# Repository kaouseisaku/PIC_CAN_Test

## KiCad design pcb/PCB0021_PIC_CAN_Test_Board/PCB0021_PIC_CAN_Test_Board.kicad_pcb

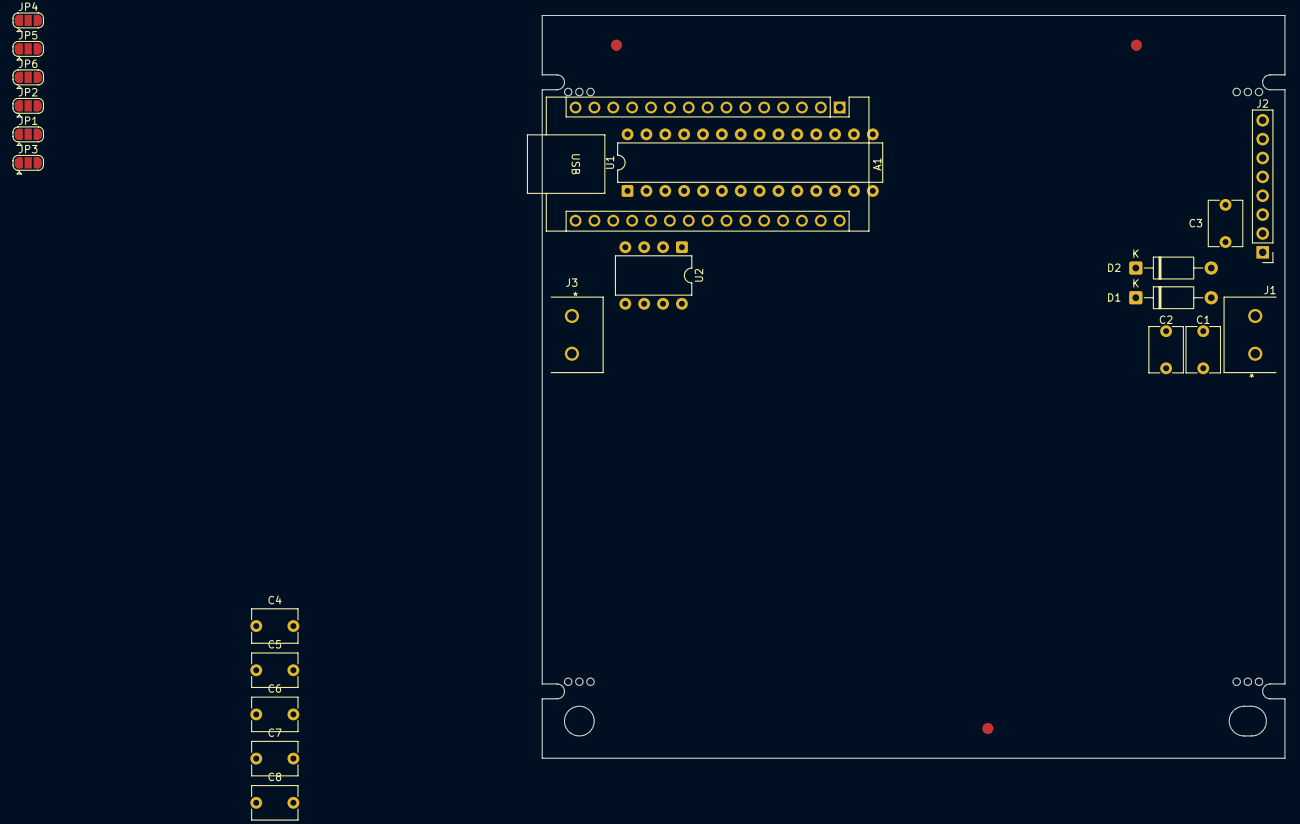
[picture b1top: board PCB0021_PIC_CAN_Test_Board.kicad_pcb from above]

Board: 2 copper layers, 100.0 x 100.0 mm, 22 parts (0 on the bottom side), 38 nets, no tracks yet.

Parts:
A1: Arduino_Nano_v3.x; Arduino_Nano
C1: 106C10; C_Disc_D6.0mm_W4.4mm_P5.00mm
C2, C3, C4, C5, C6, C7, C8: 104C10; C_Disc_D6.0mm_W4.4mm_P5.00mm
D1, D2: SBM245L; D_A-405_P10.16mm_Horizontal
J1, J3: TB111-2-2-E-1-1; TB111-2-2-X-1-1
J2: PH-1; PinHeader_1x08_P2.54mm_Vertical
JP1, JP2, JP3, JP4, JP5, JP6: Jumper_3_Open; SolderJumper-3_P1.3mm_Open_RoundedPad1.0x1.5mm
U1: PIC18F26K80_ISP; DIP-28_W7.62mm
U2: MCP2562-E-P; DIP-8_W7.62mm

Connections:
+5V: A1.27 (+5V), C4.1, C5.1, C6.1, C7.1, C8.1, D1.1 (K), D2.1 (K), U1.6 (Vcap), U1.20 (Vdd), U2.3 (VDD), U2.5 (Vio)
/AN0: A1.19 (A0), U1.2 (RA0/AN0)
/AN1: A1.20 (A1), U1.3 (RA1/AN1)
/AN2: A1.21 (A2), U1.4 (RA2/Vref-/AN2)
/AN3: A1.22 (A3), U1.5 (RA3/Vref+/AN3)
/CANRX: JP2.1 (A), U2.4 (RXD)
/CANRX/RB3: JP2.2 (C), U1.24 (CANRX/INT3/RB3)
/CANSTBY: JP3.1 (A), U2.8 (STBY)
/CANSTBY/RB4: JP3.2 (C), U1.25 (AN9/ECCP1/RB4)
/CANTX: JP1.1 (A), U2.1 (TXD)
/CANTX/RB2: JP1.2 (C), U1.23 (CANTX/INT2/RB2)
/PCG: J2.5, U1.27 (PGC/TX2/RB6)
/PGD: J2.4, U1.28 (PGD/RX2/RB7)
/RB0: A1.5 (D2), U1.21 (AN10/INT0/RB0)
/RB1: A1.6 (D3), U1.22 (AN8/INT1/RB1)
/RB2: A1.7 (D4), JP1.3 (B)
/RB3: A1.8 (D5), JP2.3 (B)
/RB4: A1.9 (D6), JP3.3 (B)
/RB5: A1.10 (D7), U1.26 (CCP5/RB5)
/RC0: A1.11 (D8), U1.11 (SOSCO/RC0)
/RC1: A1.12 (D9), U1.12 (SOSCI/RC1)
/RC2: A1.13 (D10), U1.13 (CCP2/RC2)
/SCK: A1.16 (D13), JP4.1 (A)
/SCL: A1.24 (A5), JP4.3 (B)
/SCL/SCK: JP4.2 (C), U1.14 (SCL/SCK/RC3)
/SDA: A1.23 (A4), JP5.3 (B)
/SDA/SDI: JP5.2 (C), U1.15 (SDA/SDI/RC4)
/SDI: A1.14 (D11), JP5.1 (A)
/SDO: A1.15 (D12), JP6.1 (A)
/SDO/RC5: JP6.2 (C), U1.16 (SDO/RC5)
/UART_RX: A1.2 (D0/RX), U1.18 (CANRX/RX1/CCP4/RC7)
/UART_TX: A1.1 (D1/TX), U1.17 (CANTX/TX1/CCP3/RC6)
/~MCLR: A1.3 (~RESET), A1.28 (~RESET), J2.1, U1.1 (~MCLR/RE3)
GND: A1.4 (GND), A1.29 (GND), C1.2, C2.2, C3.2, C4.2, C5.2, C6.2, C7.2, C8.2, J1.1, J2.3, U1.8 (Vss), U1.19 (Vss), U2.2 (VSS)
unnamed: J3.1, U2.7 (CANH)
unnamed: J3.2, U2.6 (CANL)
VIN1: C1.1, C2.1, D1.2 (A), J1.2
VIN2: C3.1, D2.2 (A), J2.2

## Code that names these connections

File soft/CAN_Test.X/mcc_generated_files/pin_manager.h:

/**
  @Generated Pin Manager Header File

  @Company:
    Microchip Technology Inc.

  @File Name:
    pin_manager.h

  @Summary:
    This is the Pin Manager file generated using PIC10 / PIC12 / PIC16 / PIC18 MCUs

  @Description
    This header file provides APIs for driver for .
    Generation Information :
        Product Revision  :  PIC10 / PIC12 / PIC16 / PIC18 MCUs - 1.81.8
        Device            :  PIC18F26K80
        Driver Version    :  2.11
    The generated drivers are tested against the following:
        Compiler          :  XC8 2.36 and above
        MPLAB 	          :  MPLAB X 6.00	
*/

/*
    (c) 2018 Microchip Technology Inc. and its subsidiaries. 
    
    Subject to your compliance with these terms, you may use Microchip software and any 
    derivatives exclusively with Microchip products. It is your responsibility to comply with third party 
    license terms applicable to your use of third party software (including open source software) that 
    may accompany Microchip software.
    
    THIS SOFTWARE IS SUPPLIED BY MICROCHIP "AS IS". NO WARRANTIES, WHETHER 
    EXPRESS, IMPLIED OR STATUTORY, APPLY TO THIS SOFTWARE, INCLUDING ANY 
    IMPLIED WARRANTIES OF NON-INFRINGEMENT, MERCHANTABILITY, AND FITNESS 
    FOR A PARTICULAR PURPOSE.
    
    IN NO EVENT WILL MICROCHIP BE LIABLE FOR ANY INDIRECT, SPECIAL, PUNITIVE, 
    INCIDENTAL OR CONSEQUENTIAL LOSS, DAMAGE, COST OR EXPENSE OF ANY KIND 
    WHATSOEVER RELATED TO THE SOFTWARE, HOWEVER CAUSED, EVEN IF MICROCHIP 
    HAS BEEN ADVISED OF THE POSSIBILITY OR THE DAMAGES ARE FORESEEABLE. TO 
    THE FULLEST EXTENT ALLOWED BY LAW, MICROCHIP'S TOTAL LIABILITY ON ALL 
    CLAIMS IN ANY WAY RELATED TO THIS SOFTWARE WILL NOT EXCEED THE AMOUNT 
    OF FEES, IF ANY, THAT YOU HAVE PAID DIRECTLY TO MICROCHIP FOR THIS 
    SOFTWARE.
*/

#ifndef PIN_MANAGER_H
#define PIN_MANAGER_H

/**
  Section: Included Files
*/

#include <xc.h>

#define INPUT   1
#define OUTPUT  0

#define HIGH    1
#define LOW     0

#define ANALOG      1
#define DIGITAL     0

#define PULL_UP_ENABLED      1
#define PULL_UP_DISABLED     0

// get/set RB2 procedures
#define RB2_SetHigh()            do { LATBbits.LATB2 = 1; } while(0)
#define RB2_SetLow()             do { LATBbits.LATB2 = 0; } while(0)
#define RB2_Toggle()             do { LATBbits.LATB2 = ~LATBbits.LATB2; } while(0)
#define RB2_GetValue()              PORTBbits.RB2
#define RB2_SetDigitalInput()    do { TRISBbits.TRISB2 = 1; } while(0)
#define RB2_SetDigitalOutput()   do { TRISBbits.TRISB2 = 0; } while(0)
#define RB2_SetPullup()             do { WPUBbits.WPUB2 = 1; } while(0)
#define RB2_ResetPullup()           do { WPUBbits.WPUB2 = 0; } while(0)

// get/set RB3 procedures
#define RB3_SetHigh()            do { LATBbits.LATB3 = 1; } while(0)
#define RB3_SetLow()             do { LATBbits.LATB3 = 0; } while(0)
#define RB3_Toggle()             do { LATBbits.LATB3 = ~LATBbits.LATB3; } while(0)
#define RB3_GetValue()              PORTBbits.RB3
#define RB3_SetDigitalInput()    do { TRISBbits.TRISB3 = 1; } while(0)
#define RB3_SetDigitalOutput()   do { TRISBbits.TRISB3 = 0; } while(0)
#define RB3_SetPullup()             do { WPUBbits.WPUB3 = 1; } while(0)
#define RB3_ResetPullup()           do { WPUBbits.WPUB3 = 0; } while(0)

// get/set RC3 procedures
#define RC3_SetHigh()            do { LATCbits.LATC3 = 1; } while(0)
#define RC3_SetLow()             do { LATCbits.LATC3 = 0; } while(0)
#define RC3_Toggle()             do { LATCbits.LATC3 = ~LATCbits.LATC3; } while(0)
#define RC3_GetValue()              PORTCbits.RC3
#define RC3_SetDigitalInput()    do { TRISCbits.TRISC3 = 1; } while(0)
#define RC3_SetDigitalOutput()   do { TRISCbits.TRISC3 = 0; } while(0)

// get/set RC4 procedures
#define RC4_SetHigh()            do { LATCbits.LATC4 = 1; } while(0)
#define RC4_SetLow()             do { LATCbits.LATC4 = 0; } while(0)
#define RC4_Toggle()             do { LATCbits.LATC4 = ~LATCbits.LATC4; } while(0)
#define RC4_GetValue()              PORTCbits.RC4
#define RC4_SetDigitalInput()    do { TRISCbits.TRISC4 = 1; } while(0)
#define RC4_SetDigitalOutput()   do { TRISCbits.TRISC4 = 0; } while(0)

// get/set RC6 procedures
#define RC6_SetHigh()            do { LATCbits.LATC6 = 1; } while(0)
#define RC6_SetLow()             do { LATCbits.LATC6 = 0; } while(0)
#define RC6_Toggle()             do { LATCbits.LATC6 = ~LATCbits.LATC6; } while(0)
#define RC6_GetValue()              PORTCbits.RC6
#define RC6_SetDigitalInput()    do { TRISCbits.TRISC6 = 1; } while(0)
#define RC6_SetDigitalOutput()   do { TRISCbits.TRISC6 = 0; } while(0)

// get/set RC7 procedures
#define RC7_SetHigh()            do { LATCbits.LATC7 = 1; } while(0)
#define RC7_SetLow()             do { LATCbits.LATC7 = 0; } while(0)
#define RC7_Toggle()             do { LATCbits.LATC7 = ~LATCbits.LATC7; } while(0)
#define RC7_GetValue()              PORTCbits.RC7
#define RC7_SetDigitalInput()    do { TRISCbits.TRISC7 = 1; } while(0)
#define RC7_SetDigitalOutput()   do { TRISCbits.TRISC7 = 0; } while(0)

/**
   @Param
    none
   @Returns
    none
   @Description
    GPIO and peripheral I/O initialization
   @Example
    PIN_MANAGER_Initialize();
 */
void PIN_MANAGER_Initialize (void);

/**
 * @Param
    none
 * @Returns
    none
 * @Description
    Interrupt on Change Handling routine
 * @Example
    PIN_MANAGER_IOC();
 */
void PIN_MANAGER_IOC(void);



#endif // PIN_MANAGER_H
/**
 End of File
*/
